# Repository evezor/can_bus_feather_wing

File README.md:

# can_bus_feather_wing

THIS IS A WORK IN PROGRESS. This files are not complete.
This is a can bus transiever wing for Adafruit's STM32F405 Express Feather  Place jumpers for can termination

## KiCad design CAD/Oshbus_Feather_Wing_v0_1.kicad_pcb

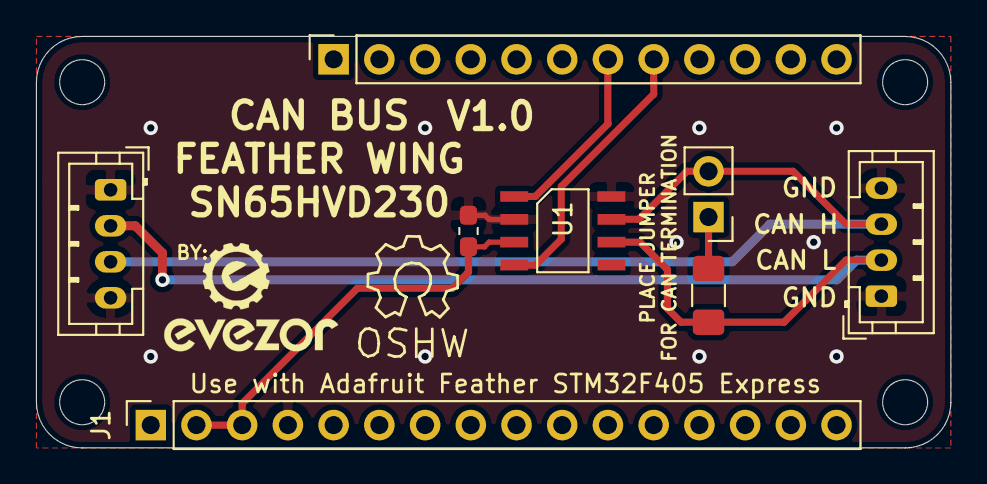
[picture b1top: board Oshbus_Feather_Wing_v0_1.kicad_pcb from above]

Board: 2 copper layers, 50.8 x 22.9 mm, 12 parts (0 on the bottom side), 7 nets.

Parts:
C2: 100nF; C_0603_1608Metric_Pad1.05x0.95mm_HandSolder
H1, H2, H3, H4: MountingHole_Pad; MountingHole_2.5mm
J1: Conn_01x16; PinSocket_1x16_P2.54mm_Vertical
J2: Conn_01x12; PinSocket_1x12_P2.54mm_Vertical
J3: JMP1; PinHeader_1x02_P2.54mm_Vertical
J4, J5: CAN_OUT; JST_PH_B4B-PH-K_1x04_P2.00mm_Vertical
R7: 120; R_1206_3216Metric_Pad1.42x1.75mm_HandSolder
U1: Trans_CAN_SN65HVD230DR; CAN-TRANS-SN65HVD230DR

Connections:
+3V3: C2.1, J1.2, J1.3, U1.3
CAN_RX: J2.8, U1.4
CAN_TX: J2.7, U1.1
GND: C2.2, J1.4, J4.1, J4.4, J5.1, J5.4, U1.2, U1.8
unnamed: J3.1, R7.1
unnamed: J3.2, J4.3, J5.3, U1.7
unnamed: J4.2, J5.2, R7.2, U1.6

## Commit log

2021-03-15 Create LICENSE
2021-03-15 add cad
